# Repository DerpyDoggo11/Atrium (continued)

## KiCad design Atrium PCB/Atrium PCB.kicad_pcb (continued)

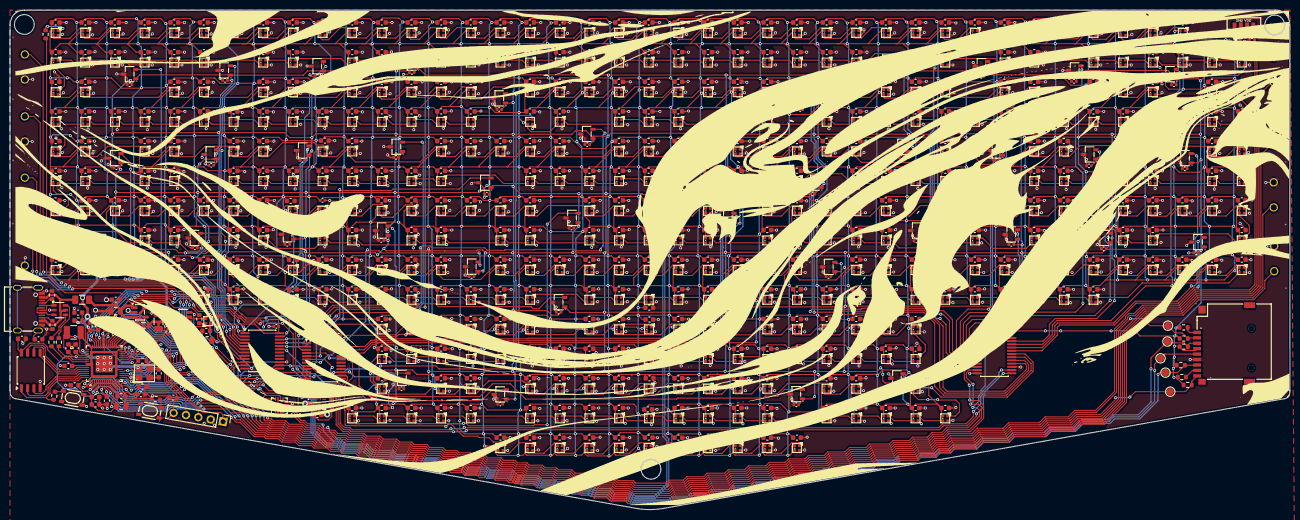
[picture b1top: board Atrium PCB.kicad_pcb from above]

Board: 2 copper layers, 259.0 x 101.1 mm, 1011 parts (1 on the bottom side), 530 nets.

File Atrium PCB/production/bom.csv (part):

Designator,Footprint,Quantity,Value,LCSC Part #
"C10, C4, C5, C6",0603,4,4.7uF,
"C100, C101, C102, C103, C104, C105, C106, C107, C108, C109, C11, C110, C111, C112, C113, C114, C115, C116, C117, C118, C119, C12, C120, C122, C123, C124, C125, C126, C127, C128, C129, C13, C130, C131, C132, C133, C134, C135, C136, C137, C138, C139, C14, C140, C141, C142, C143, C144, C145, C146, C147, C148, C149, C150, C151, C152, C153, C154, C155, C156, C158, C159, C16, C160, C161, C162, C163, C164, C165, C166, C167, C168, C169, C17, C170, C171, C172, C173, C174, C175, C176, C177, C178, C179, C18, C180, C181, C182, C183, C184, C185, C186, C187, C188, C189, C19, C191, C192, C193, C194, C195, C196, C197, C198, C199, C20, C200, C201, C202, C203, C204, C205, C206, C207, C208, C209, C21, C210, C212, C213, C214, C215, C216, C217, C218, C219, C22, C220, C221, C222, C223, C224, C225, C226, C227, C228, C23, C230, C231, C232, C233, C234, C235, C236, C237, C238, C239, C24, C240, C241, C242, C243, C244, C245, C246, C247, C248, C249, C25, C250, C251, C252, C253, C254, C255, C256, C257, C258, C259, C26, C260, C261, C262, C263, C264, C265, C266, C267, C268, C269, C270, C271, C272, C273, C274, C275, C276, C277, C278, C279, C280, C281, C282, C283, C284, C285, C286, C287, C288, C289",0603,200,100nF,
"C15, C400, C63",0805,3,10uF,
C211,0402,1,22uF,
C27,0603,1,10nF,
"C290, C291, C292, C293, C294, C295, C296, C297, C298, C299, C3, C300, C302, C303, C304, C305, C306, C307, C308, C309, C310, C311, C312, C313, C314, C315, C316, C317, C318, C319, C320, C321, C322, C323, C324, C325, C326, C327, C328, C329, C330, C331, C332, C333, C334, C335, C336, C337, C338, C339, C340, C341, C342, C343, C344, C345, C346, C347, C348, C349, C350, C351, C352, C353, C354, C355, C356, C357, C358, C359, C360, C361, C362, C363, C364, C365, C366, C367, C368, C369, C370, C371, C372, C373, C374, C375, C376, C377, C378, C379, C380, C381, C425, C426, C427, C428, C429, C430, C431, C432, C433, C434, C435, C436, C437, C438, C439, C440, C441, C442, C443, C444, C445, C446, C447, C448, C449, C450, C451, C452, C453, C454, C455, C456, C457, C458, C459, C460, C461, C462, C463, C464, C465, C466, C467, C468, C469, C470, C471, C472, C473, C474, C475, C476, C477, C478, C479, C480, C481, C482, C483, C484, C485, C486, C487, C488, C489, C490, C491, C492, C493, C494, C495, C496, C497, C498, C499, C500, C501, C502, C503, C504, C505, C506, C507, C508, C509, C510, C511, C512, C513, C514, C515, C516, C517, C518, C519, C520, C521, C522, C523, C524, C525, C526, C527, C528, C529, C530, C531, C532",0603,200,100nF,
"C301, C382, C383, C384, C385, C386, C387, C388, C389, C390, C391, C392, C393, C394, C395, C396, C397, C398, C399, C402, C403, C404, C405, C406, C407, C408, C409, C410, C411, C412, C413, C414, C415, C416, C417, C418, C419, C420, C421, C422, C423, C424, C546, C547, C548",0402,45,100nF,
C401,1206,1,100uF,
"C533, C534, C535, C536, C537, C538, C539, C540, C541, C542, C543, C544, C549, C550, C551, C552, C553, C554, C62, C64, C82, C83, C84, C85, C86, C87, C88, C89, C90, C91, C92, C93, C94, C95, C96, C97, C98, C99",0603,38,100nF,
C65,0603,1,1uF,
"C7, C8",0603,2,15pF,
C9,0603,1,1nF,
CARD1,TF-SMD_TF-PUSH,1,TF PUSH,C393941
D5,SOT-23-6_L2.9-W1.6-P0.95-LS2.8-BL,1,USBLC6-2SC6_C2687116,C2687116
F1,1206,1,3A,
FB1,0805,1,Ferrite 600R@100MHz,
FLASH1,SOIC-8_5.3x5.3mm_P1.27mm,1,W25Q128JVS,
J1,PinHeader_1x05_P2.54mm_Vertical,1,Conn_01x05_Pin,
L1,1210,1,3.3uH,
LED1,LED-SMD_4P-L6.8-W2.4_VEML7700-TR,1,VEML7700-TR,C504893
"LED10, LED100, LED101, LED102, LED103, LED104, LED105, LED106, LED107, LED108, LED109, LED11, LED110, LED111, LED112, LED113, LED114, LED115, LED116, LED117, LED118, LED119, LED12, LED120, LED121, LED123, LED124, LED125, LED126, LED127, LED128, LED129, LED13, LED130, LED131, LED132, LED133, LED134, LED135, LED136, LED137, LED138, LED139, LED14, LED140, LED141, LED142, LED143, LED144, LED146, LED147, LED148, LED149, LED15, LED150, LED151, LED152, LED153, LED154, LED155, LED156, LED157, LED158, LED159, LED16, LED160, LED161, LED162, LED163, LED164, LED166, LED167, LED168, LED169, LED17, LED170, LED171, LED172, LED173, LED174, LED175, LED176, LED177, LED178, LED179, LED18, LED180, LED181, LED182, LED183, LED184, LED185, LED186, LED187, LED188, LED189, LED19, LED190, LED191, LED192, LED193, LED194, LED195, LED196, LED197, LED198, LED199, LED2, LED20, LED200, LED201, LED202, LED203, LED204, LED205, LED206, LED207, LED208, LED209, LED21, LED210, LED211, LED212, LED213, LED214, LED215, LED216, LED217, LED218, LED219, LED22, LED220, LED221, LED222, LED223, LED224, LED225, LED226, LED227, LED228, LED229, LED23, LED230, LED231, LED232, LED233, LED234, LED235, LED236, LED237, LED238, LED239, LED24, LED240, LED241, LED242, LED243, LED244, LED245, LED246, LED247, LED248, LED249, LED25, LED250, LED251, LED252, LED253, LED254, LED255, LED256, LED257, LED258, LED259, LED26, LED260, LED261, LED262, LED263, LED264, LED265, LED266, LED267, LED268, LED269, LED27, LED270, LED271, LED272, LED273, LED274, LED275, LED276, LED277, LED278, LED279, LED28, LED280, LED281, LED282",LED-SMD_4P-L1.5-W1.5-BL,200,SK6805-EC15,C2890035
"LED283, LED284, LED285, LED286, LED287, LED288, LED289, LED29, LED290, LED291, LED292, LED293, LED294, LED295, LED296, LED297, LED298, LED299, LED3, LED30, LED300, LED301, LED302, LED303, LED304, LED305, LED306, LED307, LED308, LED309, LED31, LED310, LED311, LED312, LED313, LED314, LED315, LED316, LED317, LED318, LED319, LED32, LED320, LED321, LED322, LED323, LED324, LED325, LED326, LED327, LED328, LED329, LED33, LED330, LED331, LED332, LED333, LED334, LED335, LED336, LED337, LED338, LED339, LED34, LED340, LED341, LED342, LED343, LED344, LED345, LED346, LED347, LED348, LED349, LED35, LED350, LED351, LED352, LED353, LED354, LED355, LED356, LED357, LED358, LED359, LED36, LED360, LED361, LED362, LED363, LED364, LED365, LED366, LED367, LED368, LED369, LED37, LED370, LED371, LED372, LED373, LED374, LED375, LED376, LED377, LED378, LED379, LED38, LED380, LED381, LED382, LED383, LED384, LED385, LED386, LED387, LED388, LED389, LED39, LED390, LED391, LED392, LED393, LED394, LED395, LED396, LED399, LED4, LED40, LED402, LED41, LED411, LED414, LED42, LED426, LED43, LED435, LED436, LED437, LED439, LED44, LED440, LED441, LED442, LED443, LED447, LED448, LED449, LED45, LED451, LED452, LED453, LED454, LED459, LED46, LED460, LED463, LED464, LED466, LED47, LED471, LED472, LED475, LED476, LED477, LED478, LED48, LED49, LED5, LED50, LED51, LED52, LED53, LED54, LED55, LED56, LED57, LED58, LED59, LED6, LED60, LED61, LED62, LED63, LED64, LED65, LED66, LED67, LED68, LED69, LED7, LED70, LED71, LED72, LED73, LED74, LED75, LED76, LED77, LED78",LED-SMD_4P-L1.5-W1.5-BL,200,SK6805-EC15,C2890035
"LED79, LED8, LED80, LED81, LED82, LED83, LED84, LED85, LED87, LED88, LED89, LED9, LED90, LED91, LED92, LED93, LED94, LED95, LED96, LED97, LED98, LED99",LED-SMD_4P-L1.5-W1.5-BL,22,SK6805-EC15,C2890035
"R10, R13",0603,2,470,
"R28, R29, R30, R31, R36, R37",0603,6,10k,
"R3, R7, R8",0603,3,1k,
"R32, R33",0603,2,5.1k,
"R34, R35",0603,2,27,
"R40, R41",0402,2,4.7k,
R6,0603,1,33,
RP2350,QFN-60-1EP_7x7mm_P0.4mm_EP3.4x3.4mm,1,RP2350A,
SPK1,SPK-TH_BD23.0-P10.00-D0.8-L-RD,1,GSPK2308P-8R0.5W,f
"SW2, SW3",KEY-SMD_4P-L4.2-W3.2-P2.20-LS4.6,2,SKRPACE010,C139797
"SW41, SW49, SW55, SW56, SW57, SW58, SW59, SW60",SW-TH_FG-TC-12E-02-8H,8,FG-TC-12E-02-8H,C54141282
"TP18, TP19, TP20, TP21, TP22",TestPoint_Pad_D1.5mm,5,Breakout,
"U1, U10, U11, U13, U14, U15, U16, U17, U19, U20, U21, U22, U23, U24, U25, U27, U28, U29, U30, U31, U32, U33, U34, U35, U36, U37, U38, U39, U4, U40, U41, U42, U44, U45, U46, U47, U5, U7, U8, U9",SOT-23-3_L2.9-W1.6-P1.90-LS2.8-BR,40,CH604ASR,C2830877
U12,SOT-23-5,1,AP2112K-3.3,
"U18, U3, U43",SSOP-24_5.3x8.2mm_P0.65mm,3,CD74HC4067SM,
U2,LGA-14_L3.0-W2.5-P0.50-TL,1,LSM6DS3TR-C,C967633
U48,TQFN-16-1EP_3x3mm_P0.5mm_EP1.23x1.23mm,1,MAX98357A,
U6,SOT-23-6_L2.9-W1.6-P0.95-LS2.8-BR,1,SN74LVC1T45DBVR,C7843
USB1,USB-C_SMD-TYPE-C-31-M-12,1,USB-TYPE-C-018,C2927038
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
